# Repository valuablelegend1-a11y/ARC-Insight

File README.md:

# ARC-Insight 

## What it is:

ARC-Insight is a pair of AI glasses that directly connect to my homemade prompt transformer based AI: J.A.R.V.I.S. The frames carry the extensive payload of two bone conduction transducers for audio output, INMP441 and electret mics for audio input, a MAX30102 heart rate sensor for direct vitals tracking and emotion mapping, an OV2640 camera module for facial and object recognition, two 300mAh LiPo batteries for at least a full day of battery life at moderate usage, and to tie it all together; a custom ESP32-S3 based PCB!

The goal is a digital assistant that can come with me everywhere, while also expanding the abilities of Jarvis to do some things he couldn't from my desktop. He will be able to do things like answer personal questions, find search results, tell me what I'm holding or looking at, tell me who the person in front of me is, open up apps on my PC, start 3D prints, and even more. All while mapping my heartrate and speech patterns to respond with a genuine conversational feel through the GPT(NOT ChatGPT, they may have popularized the name GPT, but it just means a Generative Prompt Transformer, which is what Jarvis's speech is using).  

## How to use it:

First a quick primer, because this whole thing is two halves that have to work together, you have the glasses, which are the dumb half on purpose, they just record (microphone, camera, and your heart rate) and stream it all over Wi-Fi, and then you have Jarvis, which is the smart half, a desktop AI assistant I've been building for a while now, he's a custom language model with tools for things like object recognition, memory, web search, and much much more (I'm still deciding whether to ever make him open source, but if I do I'll drop a link here), and he does all the actual thinking and streams his reply back to the glasses so you hear it in your ears. Neither half is useful alone, you need both.

Setup happens in two places, and you only really do it once, the glasses and the PC.

The glasses half, the firmware lives in this repo at Code/firmware, you open it in PlatformIO (a coding tool for microcontrollers, sort of like a much more powerful Arduino IDE, it handles the build and the libraries for you), and before you build it the first time you need to put your Wi-Fi name and password, plus the address of the PC that runs Jarvis, into the little config file at Code/firmware/arcinsight_config.h (there are blanks right where they belong, you can't miss them), and then you plug the glasses in over USB, hit build and upload, and that's the only time you'll ever need a cable. After that the glasses just need power and to be on the same Wi-Fi as the PC, and they take care of themselves.

The PC half, you need Jarvis running (same desk assistant I mentioned, the glasses really are just a remote control for him), and you drop this arc_insight package into the same folder as the rest of his code, where it plugs in with a few lines and doesn't touch anything else (that was the whole design goal, he behaves exactly the same until the glasses show up), then you just start him up like normal, and when the glasses connect you'll see `ARCINSIGHT: glasses connected` in the console, and you're off.

Once they're connected it's all voice, you say "jarvis" (the same wake word you might already use at the desk, it becomes a habit fast) followed by whatever you need, like "what do you see", "who is this", "take a picture", or "how am I feeling", the last one is the heart rate sensor earning its keep, Jarvis reads your heartbeat, mixes it with the tone of what you said, and guesses if you're stressed or excited or just having a chill day, which is honestly the feature I'm most excited to see working. You can jump between the glasses and the desk whenever you want too, just say "jarvis, switch to glasses" or "jarvis, switch to laptop", or press Ctrl+Alt+G (the hotkey, it's easy to remap in the config), and Jarvis moves his ears, his mouth, and his eyes to wherever you are.

And when a newer firmware comes out, the cable stays in the drawer, you build the new image and run one little command, `python arc_insight\ota.py --bin ..\arc-insight\Code\.pio\build\arcinsight\firmware.bin`, and it streams the update over Wi-Fi on the same connection, the glasses verify it and reboot into the new version (if it fails the check they just stay on the old one, which is a nice safety net).

## Why I am building this:

- To learn real firmware development, power management, and how to package electronics into a wearable.
- To take Jarvis with me instead of keeping him chained to the desk.
- The heartbeat + speech sentiment combo lets Jarvis react to *how* I say things, not just *what* I say.

## Notes:

1. This is the first version of this project, so some things will change in future versions, like for instance the code may be optimized to run everything locally on the device, but that is not yet(look at note 3 for more information).
2. The code will not be all just written from memory for me for it all, I am still learning to code in general. That said, I really am diving deep into this, but it will still have some copy and paste from Google search, reddit snippets, or anything I need to make it work that I don't know.
3. Version 0 of this project is designed to be mostly a peripheral to my AI assistant J.A.R.V.I.S., who is a custom made Generative Prompt Transformer(GPT) based off of NanoGPT by Andrej Karpathy, with added tools for things like image and object recognition, memory, web search, and much much more. For more detail on that I will soon be making a repo to document that journey and how the AI runs now.
4. This is my first time designing a custom PCB, so forgive me if it is messy and not optimized, but I am quite proud of it and I think it will function how needed for this version.

## Assembly:

## Scehmatic:

## PCB:

## PCB Render:

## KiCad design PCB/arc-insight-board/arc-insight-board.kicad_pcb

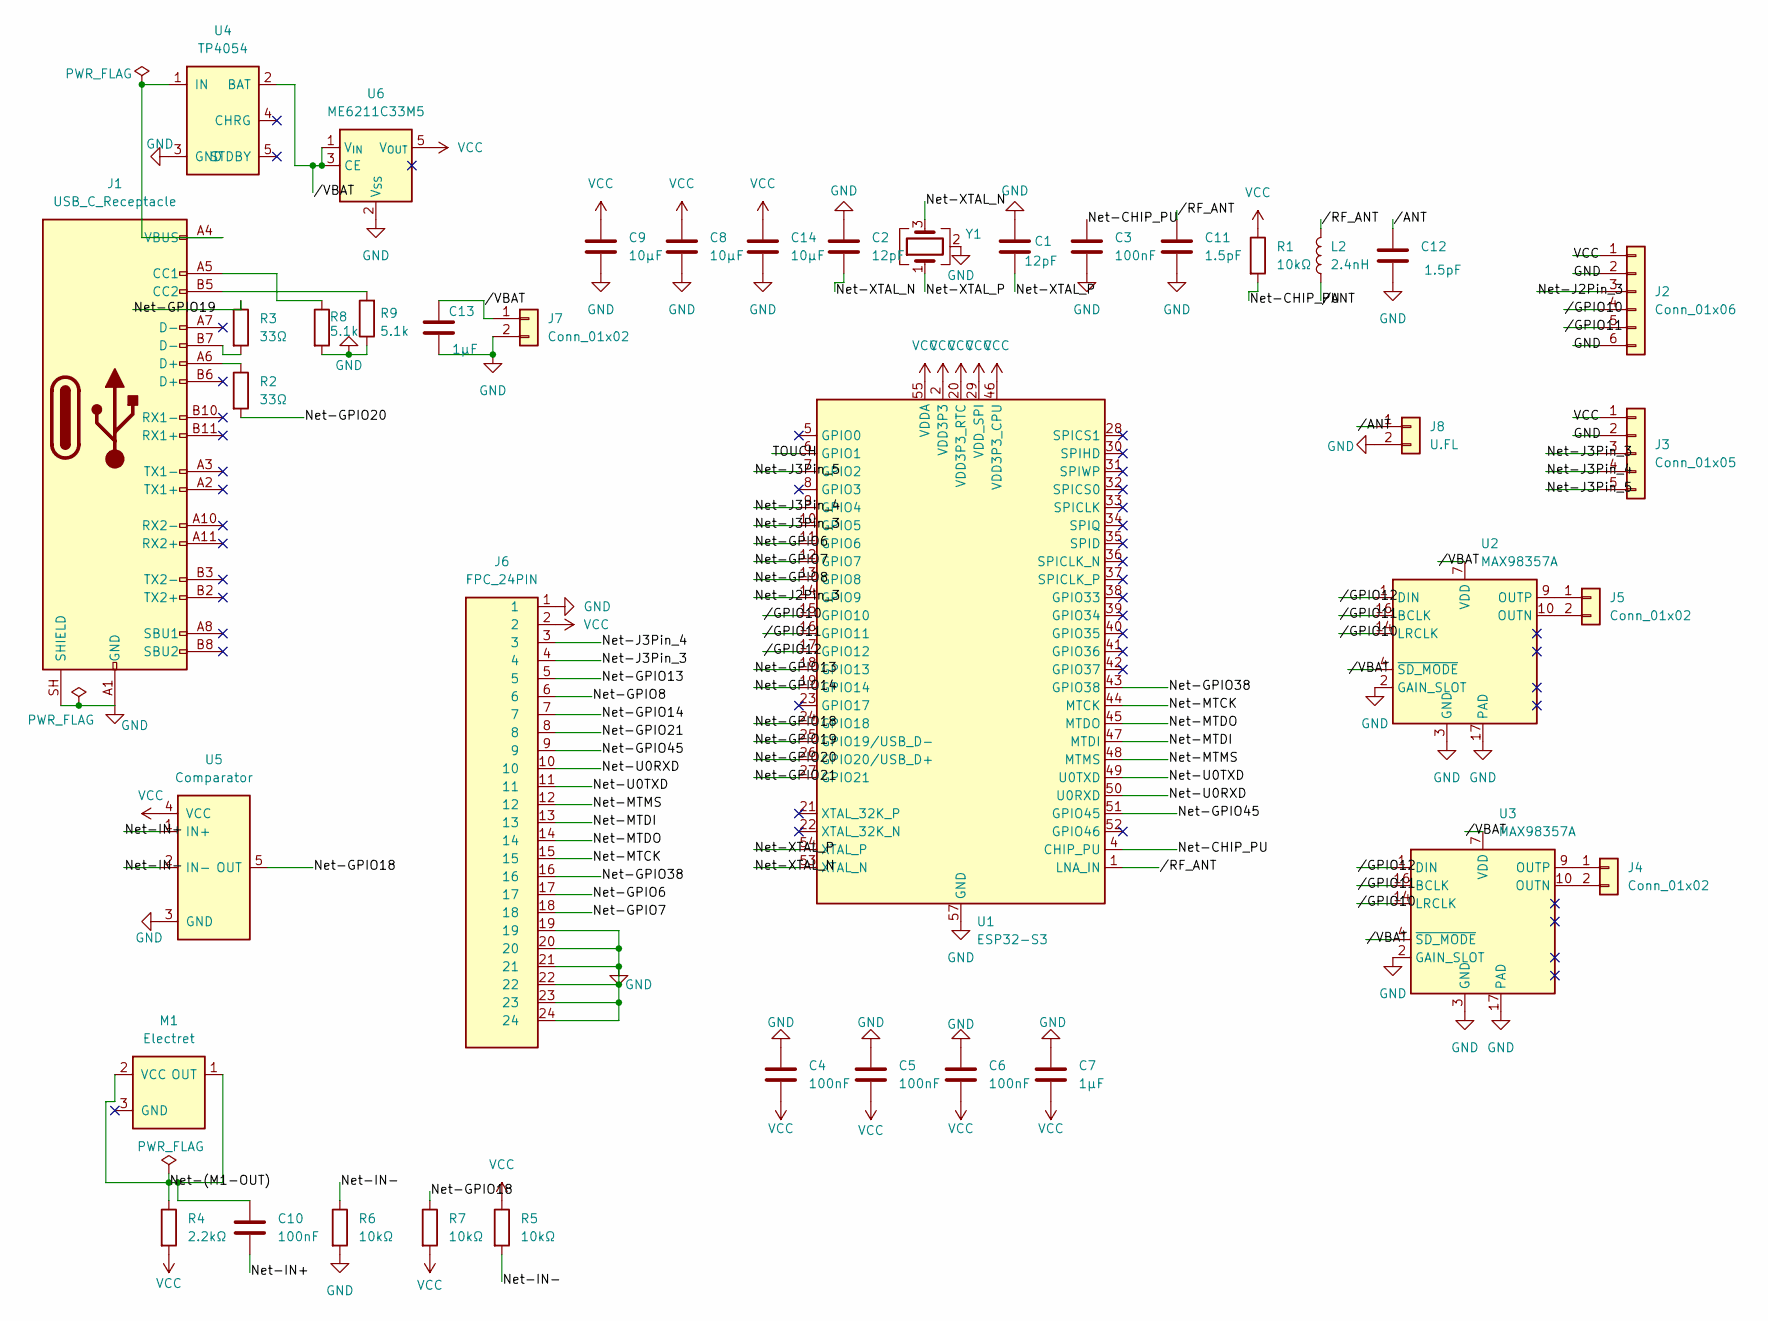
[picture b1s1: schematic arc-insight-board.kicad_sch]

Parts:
C1, C2: 12pF; C_0402_1005Metric
C3, C4, C5, C6, C10: 100nF; C_0402_1005Metric
C7: 1µF; C_0402_1005Metric
C8, C9, C14: 10µF; C_0603_1608Metric
C11, C12: 1.5pF; C_0402_1005Metric
C13: 1µF; C_0603_1608Metric
J1: USB_C_Receptacle; USB_C_Receptacle_GCT_USB4105-xx-A_16P_TopMnt_Horizontal
J2: Conn_01x06; R_Array_Convex_8x0602
J3: Conn_01x05; R_Array_Convex_5x0603
J4, J5, J7: Conn_01x02; SolderWire-0.5sqmm_1x02_P4.6mm_D0.9mm_OD2.1mm
J6: FPC_24PIN; Hirose_FH12-24S-0.5SH_1x24-1MP_P0.50mm_Horizontal
J8: U.FL; U.FL_Hirose_U.FL-R-SMT-1_Vertical
L2: 2.4nH; L_0402_1005Metric
M1: Electret; CUI_CMC-4013-SMT
R1, R5, R6, R7: 10kΩ; R_0402_1005Metric
R2, R3: 33Ω; R_0402_1005Metric
R4: 2.2kΩ; R_0402_1005Metric
R8, R9: 5.1k; R_0402_1005Metric
U1: ESP32-S3; QFN-56-1EP_7x7mm_P0.4mm_EP4x4mm
U2, U3: MAX98357A; TQFN-16-1EP_3x3mm_P0.5mm_EP1.23x1.23mm
U4: TP4054; SOT-23-5
U5: Comparator; SOT-23-5
U6: ME6211C33M5; SOT-23-5
Y1: 40MHz; Crystal_SMD_2520-4Pin_2.5x2.0mm; LCSC Part # C37635359

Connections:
/Net-(M1-OUT): C10.1, M1.1 (OUT), M1.2 (VCC), R4.1
/Net-CHIP_PU: C3.1, R1.2, U1.4 (CHIP_PU)
/Net-GPIO6: J6.17, U1.11 (GPIO6)
/Net-GPIO7: J6.18, U1.12 (GPIO7)
/Net-GPIO8: J6.6, U1.13 (GPIO8)
/Net-GPIO13: J6.5, U1.18 (GPIO13)
/Net-GPIO14: J6.7, U1.19 (GPIO14)
/Net-GPIO18: R7.1, U1.24 (GPIO18), U5.5 (OUT)
/Net-GPIO19: R3.1, U1.25 (GPIO19/USB_D-)
/Net-GPIO20: R2.2, U1.26 (GPIO20/USB_D+)
/Net-GPIO21: J6.8, U1.27 (GPIO21)
/Net-GPIO38: J6.16, U1.43 (GPIO38)
/Net-GPIO45: J6.9, U1.51 (GPIO45)
/Net-IN+: C10.2, U5.1 (IN+)
/Net-IN-: R5.2, R6.1, U5.2 (IN-)
/Net-J2Pin_3: J2.3, U1.14 (GPIO9)
/Net-J3Pin_3: J3.3, J6.4, U1.10 (GPIO5)
/Net-J3Pin_4: J3.4, J6.3, U1.9 (GPIO4)
/Net-J3Pin_5: J3.5, U1.7 (GPIO2)
/Net-MTCK: J6.15, U1.44 (MTCK)
/Net-MTDI: J6.13, U1.47 (MTDI)
/Net-MTDO: J6.14, U1.45 (MTDO)
/Net-MTMS: J6.12, U1.48 (MTMS)
/Net-U0RXD: J6.10, U1.50 (U0RXD)
/Net-U0TXD: J6.11, U1.49 (U0TXD)
/Net-XTAL_N: C2.2, U1.53 (XTAL_N), Y1.3
/Net-XTAL_P: C1.1, U1.54 (XTAL_P), Y1.1
/TOUCH: U1.6 (GPIO1); also elsewhere on the board
//ANT: C12.1, J8.1, L2.1
//GPIO10: J2.4, U1.15 (GPIO10), U2.14 (LRCLK), U3.14 (LRCLK)
//GPIO11: J2.5, U1.16 (GPIO11), U2.16 (BCLK), U3.16 (BCLK)
//GPIO12: U1.17 (GPIO12), U2.1 (DIN), U3.1 (DIN)
//RF_ANT: C11.1, L2.2, U1.1 (LNA_IN)
//VBAT: C13.1, J7.1, U2.4 (~SD_MODE), U2.7 (VDD), U2.8 (VDD), U3.4 (~SD_MODE), U3.7 (VDD), U3.8 (VDD), U4.2 (BAT), U6.1 (V_{IN}), U6.3 (CE)
GND: C1.2, C2.1, C3.2, C4.1, C5.1, C6.1, C7.1, C8.2, C9.2, C11.2, C12.2, C13.2, C14.2, J1.A1 (GND), J1.A12 (GND), J1.B1 (GND), J1.B12 (GND), J1.SH (SHIELD), J2.2, J2.6, J3.2, J6.1, J6.19, J6.20, J6.21, J6.22, J6.23, J6.24, J7.2, J8.2, R6.2, R8.2, R9.1, U1.57 (GND), U2.2 (GAIN_SLOT), U2.3 (GND), U2.11 (GND), U2.15 (GND), U2.17 (PAD), U3.2 (GAIN_SLOT), U3.3 (GND), U3.11 (GND), U3.15 (GND), U3.17 (PAD), U4.3 (GND), U5.3 (GND), U6.2 (V_{SS}), Y1.2 (G), Y1.4 (G)
unnamed: J1.A5 (CC1), R8.1
unnamed: J1.B5 (CC2), R9.2
unnamed: J1.A6 (D+), R2.1
unnamed: J1.B7 (D-), R3.2
unnamed: J4.1, U3.9 (OUTP)
unnamed: J4.2, U3.10 (OUTN)
unnamed: J5.1, U2.9 (OUTP)
unnamed: J5.2, U2.10 (OUTN)
unnamed: J1.A4 (VBUS), J1.A9 (VBUS), J1.B4 (VBUS), J1.B9 (VBUS), U4.1 (IN)
VCC: C4.2, C5.2, C6.2, C7.2, C8.1, C9.1, C14.1, J2.1, J3.1, J6.2, R1.1, R4.2, R5.1, R7.2, U1.2 (VDD3P3), U1.3 (VDD3P3), U1.20 (VDD3P3_RTC), U1.29 (VDD_SPI), U1.46 (VDD3P3_CPU), U1.55 (VDDA), U1.56 (VDDA), U5.4 (VCC), U6.5 (V_{OUT})

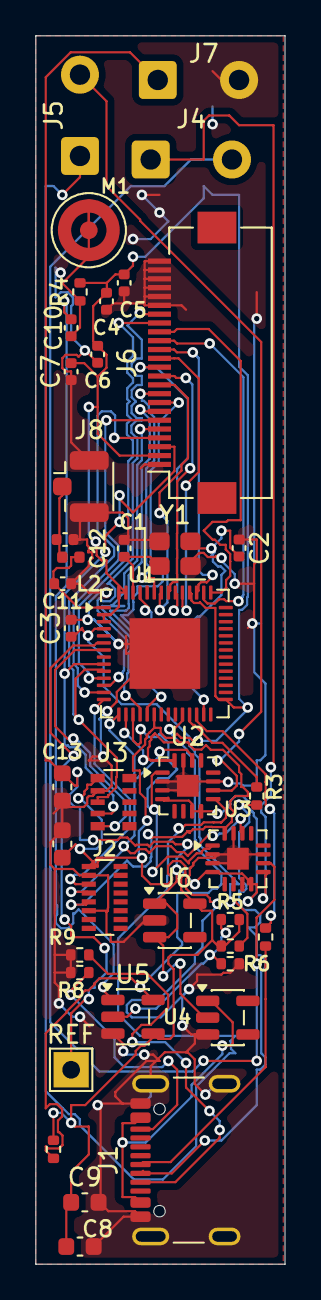
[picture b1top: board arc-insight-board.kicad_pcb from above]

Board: 2 copper layers, 14.1 x 69.5 mm, 41 parts (0 on the bottom side), 45 nets.

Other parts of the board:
REF: TestPoint_THTPad_2.0x2.0mm_Drill1.0mm

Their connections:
/TOUCH: REF.1; also elsewhere on the board

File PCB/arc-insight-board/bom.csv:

"Reference","Qty","Value","DNP","Exclude from BOM","Exclude from Board","Exclude from Simulation","Exclude from Position Files","Footprint","Datasheet"
"C1,C2","2","12pF","","","","","${EXCLUDE_FROM_POS_FILES}","Capacitor_SMD:C_0402_1005Metric",""
"C3,C4,C5,C6,C10","5","100nF","","","","","${EXCLUDE_FROM_POS_FILES}","Capacitor_SMD:C_0402_1005Metric",""
"C7","1","1µF","","","","","${EXCLUDE_FROM_POS_FILES}","Capacitor_SMD:C_0402_1005Metric",""
"C8,C9,C14","3","10µF","","","","","${EXCLUDE_FROM_POS_FILES}","Capacitor_SMD:C_0603_1608Metric",""
"C11,C12","2","1.5pF","","","","","${EXCLUDE_FROM_POS_FILES}","Capacitor_SMD:C_0402_1005Metric",""
"C13","1","1µF","","","","","${EXCLUDE_FROM_POS_FILES}","Capacitor_SMD:C_0603_1608Metric",""
"J1","1","USB_C_Receptacle","","","","","${EXCLUDE_FROM_POS_FILES}","Connector_USB:USB_C_Receptacle_GCT_USB4105-xx-A_16P_TopMnt_Horizontal","https://www.usb.org/sites/default/files/documents/usb_type-c.zip"
"J2","1","Conn_01x06","","","","","${EXCLUDE_FROM_POS_FILES}","Resistor_SMD:R_Array_Convex_8x0602",""
"J3","1","Conn_01x05","","","","","${EXCLUDE_FROM_POS_FILES}","Resistor_SMD:R_Array_Convex_5x0603",""
"J4,J5,J7","3","Conn_01x02","","","","","${EXCLUDE_FROM_POS_FILES}","Connector_Wire:SolderWire-0.5sqmm_1x02_P4.6mm_D0.9mm_OD2.1mm",""
"J6","1","FPC_24PIN","","","","","${EXCLUDE_FROM_POS_FILES}","Connector_FFC-FPC:Hirose_FH12-24S-0.5SH_1x24-1MP_P0.50mm_Horizontal",""
"J8","1","U.FL","","","","","${EXCLUDE_FROM_POS_FILES}","Connector_Coaxial:U.FL_Hirose_U.FL-R-SMT-1_Vertical",""
"L2","1","2.4nH","","","","","${EXCLUDE_FROM_POS_FILES}","Inductor_SMD:L_0402_1005Metric",""
"M1","1","Electret","","","","","${EXCLUDE_FROM_POS_FILES}","Sensor_Audio:CUI_CMC-4013-SMT",""
"R1,R5,R6,R7","4","10kΩ","","","","","${EXCLUDE_FROM_POS_FILES}","Resistor_SMD:R_0402_1005Metric",""
"R2,R3","2","33Ω","","","","","${EXCLUDE_FROM_POS_FILES}","Resistor_SMD:R_0402_1005Metric",""
"R4","1","2.2kΩ","","","","","${EXCLUDE_FROM_POS_FILES}","Resistor_SMD:R_0402_1005Metric",""
"R8,R9","2","5.1k","","","","","${EXCLUDE_FROM_POS_FILES}","Resistor_SMD:R_0402_1005Metric",""
"U1","1","ESP32-S3","","","","","${EXCLUDE_FROM_POS_FILES}","Package_DFN_QFN:QFN-56-1EP_7x7mm_P0.4mm_EP4x4mm","https://www.espressif.com/sites/default/files/documentation/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"
"U2,U3","2","MAX98357A","","","","","${EXCLUDE_FROM_POS_FILES}","Package_DFN_QFN:TQFN-16-1EP_3x3mm_P0.5mm_EP1.23x1.23mm","https://www.analog.com/media/en/technical-documentation/data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"
"U4","1","TP4054","","","","","${EXCLUDE_FROM_POS_FILES}","Package_TO_SOT_SMD:SOT-23-5",""
"U5","1","Comparator","","","","","${EXCLUDE_FROM_POS_FILES}","Package_TO_SOT_SMD:SOT-23-5",""
"U6","1","ME6211C33M5","","","","","${EXCLUDE_FROM_POS_FILES}","Package_TO_SOT_SMD:SOT-23-5","https://www.lcsc.com/datasheet/lcsc_datasheet_2304140030_MIC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"
"Y1","1","40MHz","","","","","${EXCLUDE_FROM_POS_FILES}","Crystal:Crystal_SMD_3215-2Pin_3.2x1.5mm",""
